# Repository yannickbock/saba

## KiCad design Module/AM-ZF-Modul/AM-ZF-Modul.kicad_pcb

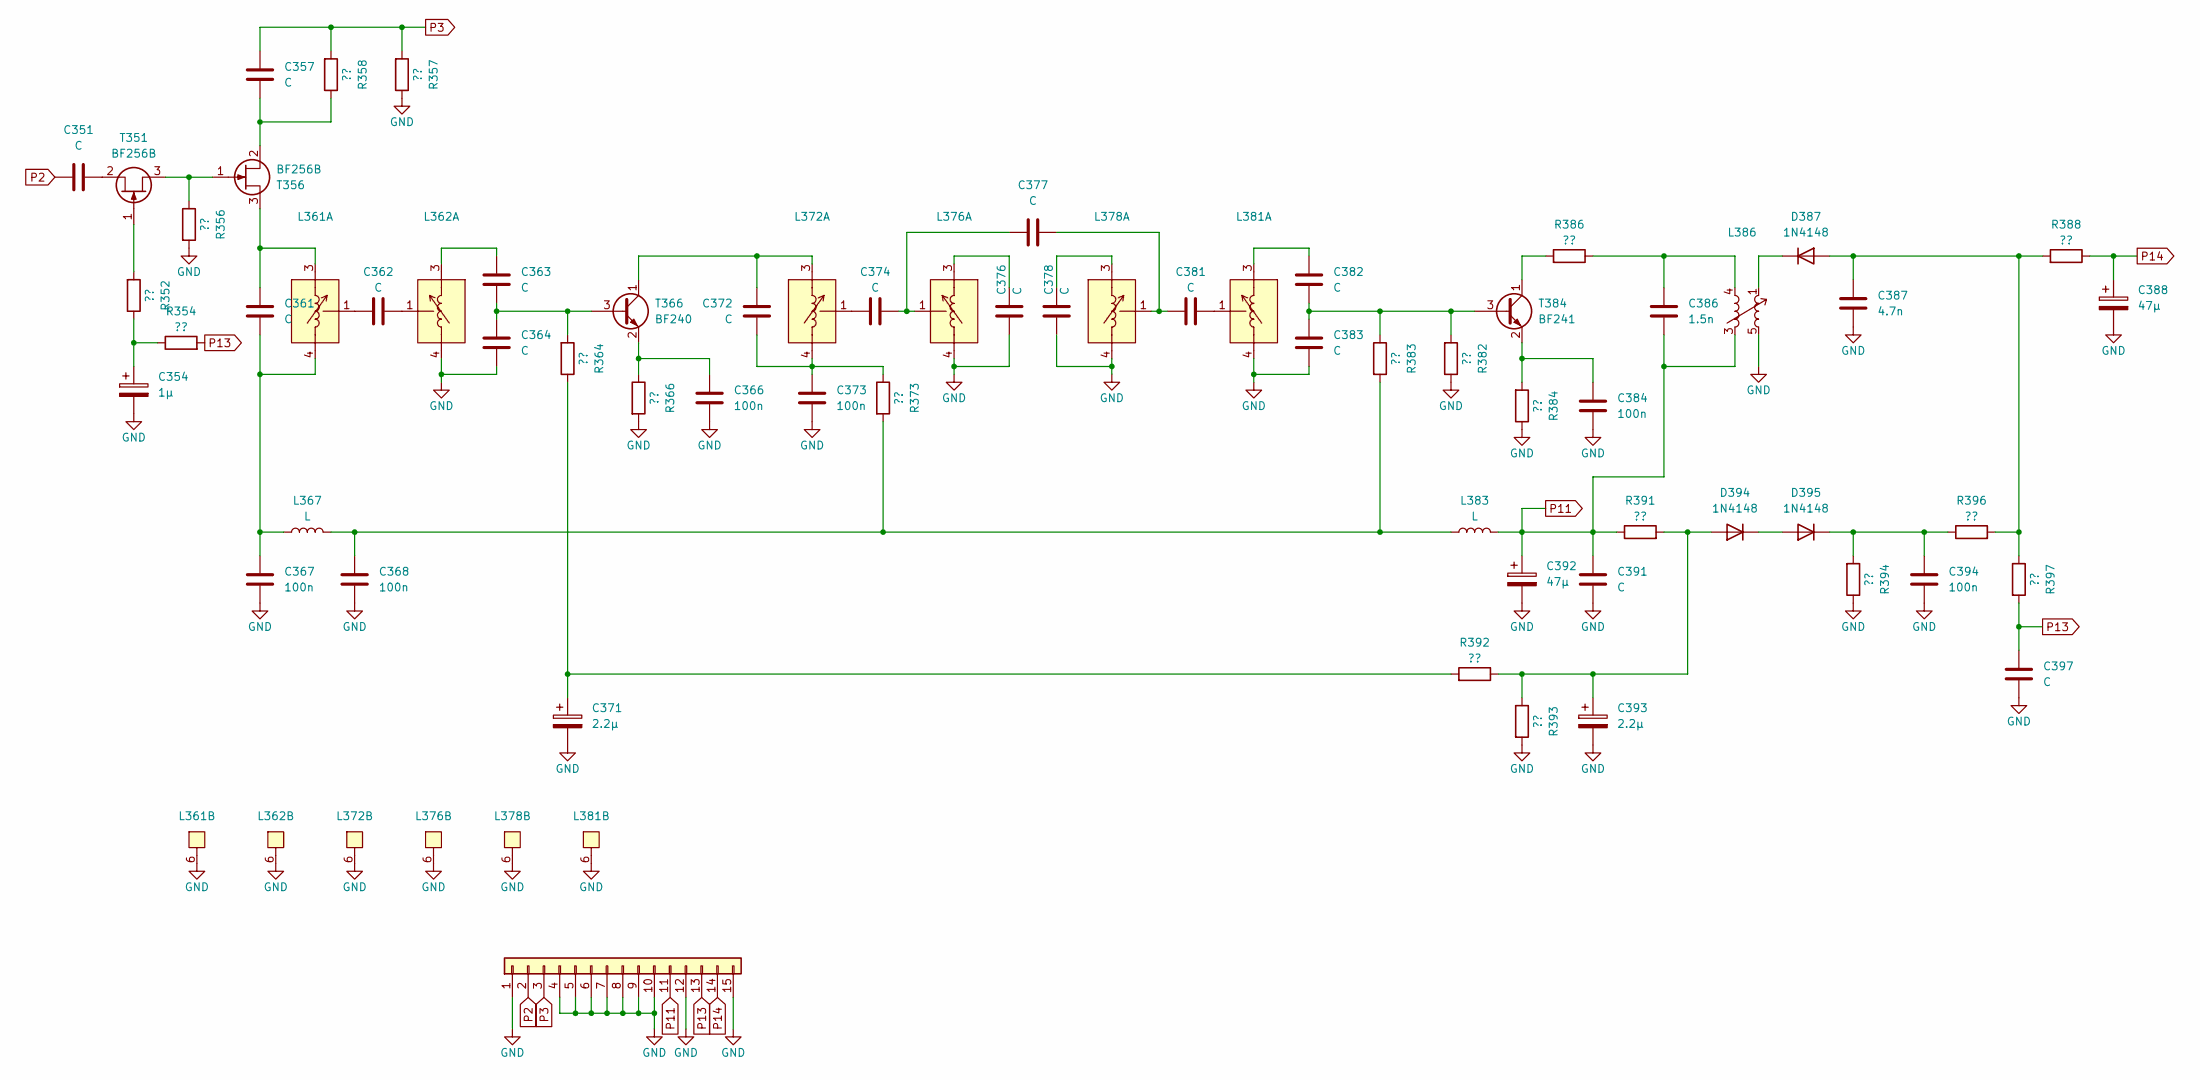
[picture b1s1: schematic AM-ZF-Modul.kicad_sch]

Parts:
C351, C397: C; C_Disc_D4.3mm_W1.9mm_P5.00mm
C354: 1µ; C_Rect_L7.2mm_W7.2mm_P5.00mm_FKS2_FKP2_MKS2_MKP2
C357, C364, C383: C; C_Rect_L7.0mm_W2.5mm_P5.00mm
C361, C362, C363, C372, C374, C376, C377, C378, C381, C382: C; L_Axial_L7.0mm_D3.3mm_P5.08mm_Vertical_Fastron_MICC
C366, C367, C368, C373, C384: 100n; C_Rect_L7.0mm_W2.5mm_P5.00mm
C371, C393: 2.2µ; CP_Radial_D5.0mm_P2.00mm
C386: 1.5n; L_Axial_L7.0mm_D3.3mm_P5.08mm_Vertical_Fastron_MICC
C387: 4.7n; C_Disc_D4.3mm_W1.9mm_P5.00mm
C388, C392: 47µ; CP_Radial_D6.3mm_P2.50mm
C391: C; C_Rect_L7.2mm_W4.5mm_P5.00mm_FKS2_FKP2_MKS2_MKP2
C394: 100n; C_Disc_D4.3mm_W1.9mm_P5.00mm
D387, D394, D395: 1N4148; D_DO-35_SOD27_P5.08mm_Vertical_AnodeUp
J1: Conn_01x15; Connector_01x15_5mm
L361, L362, L378, L381: (no value)
L367, L383: L; L_Axial_L7.0mm_D3.3mm_P5.08mm_Vertical_Fastron_MICC
L372, L376: Inductor_Adjustable_7.5mm
L386: L_Adjustable_4Pin; Inductor_Adjustable_7.5mm
R352, R354, R356, R357, R358, R364, R366, R373, R382, R383, R384, R386, R388, R391, R392, R393, R394, R396, R397: ??; R_Axial_DIN0207_L6.3mm_D2.5mm_P5.08mm_Vertical
T351, T356: BF256B; TO-92_Wide
T366: BF240; TO-92_Wide
T384: BF241; TO-92_Wide

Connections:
GND: C354.2, C364.2, C366.2, C367.2, C368.2, C371.2, C373.2, C376.2, C378.2, C383.2, C384.2, C387.2, C388.2, C391.2, C392.2, C393.2, C394.2, C397.2, J1.1, J1.4, J1.5, J1.6, J1.7, J1.8, J1.9, J1.10, J1.12, J1.15, L361.6, L362.4, L362.6, L372.6, L376.4, L376.6, L378.4, L378.6, L381.4, L381.6, L386.5, L386.6, R356.2, R357.1, R366.2, R382.1, R384.1, R393.2, R394.1
unnamed: C354.1, R352.1, R354.1
unnamed: C361.2, C367.1, L361.4, L367.2
unnamed: C362.1, L361.1
unnamed: C362.2, L362.1
unnamed: C363.1, L362.3
unnamed: C368.1, L367.1, L383.2, R373.2, R383.2
unnamed: C371.1, R364.1, R392.2
unnamed: C372.2, C373.1, L372.4, R373.1
unnamed: C374.1, L372.1
unnamed: C374.2, C377.1, L376.1
unnamed: C376.1, L376.3
unnamed: C377.2, C381.1, L378.1
unnamed: C378.1, L378.3
unnamed: C381.2, L381.1
unnamed: C382.1, L381.3
unnamed: C386.1, L386.4, R386.1
unnamed: C387.1, D387.2 (A), R388.2, R396.2, R397.1
unnamed: D387.1 (K), L386.1
unnamed: C393.1, D394.2 (A), R391.2, R392.1, R393.1
unnamed: D394.1 (K), D395.2 (A)
unnamed: C394.1, D395.1 (K), R394.2, R396.1
unnamed: R356.1, T351.3 (D), T356.1 (G)
unnamed: R352.2, T351.1 (G)
unnamed: C351.2, T351.2 (S)
unnamed: C361.1, L361.3, T356.3 (D)
unnamed: C357.2, R358.1, T356.2 (S)
unnamed: C363.2, C364.1, R364.2, T366.3 (B)
unnamed: C372.1, L372.3, T366.1 (C)
unnamed: C366.1, R366.1, T366.2 (E)
unnamed: C382.2, C383.1, R382.2, R383.1, T384.3 (B)
unnamed: R386.2, T384.1 (C)
unnamed: C384.1, R384.2, T384.2 (E)
P2: C351.1, J1.2
P3: C357.1, J1.3, R357.2, R358.2
P11: C386.2, C391.1, C392.1, J1.11, L383.1, L386.3, R391.1
P13: C397.1, J1.13, R354.2, R397.2
P14: C388.1, J1.14, R388.1

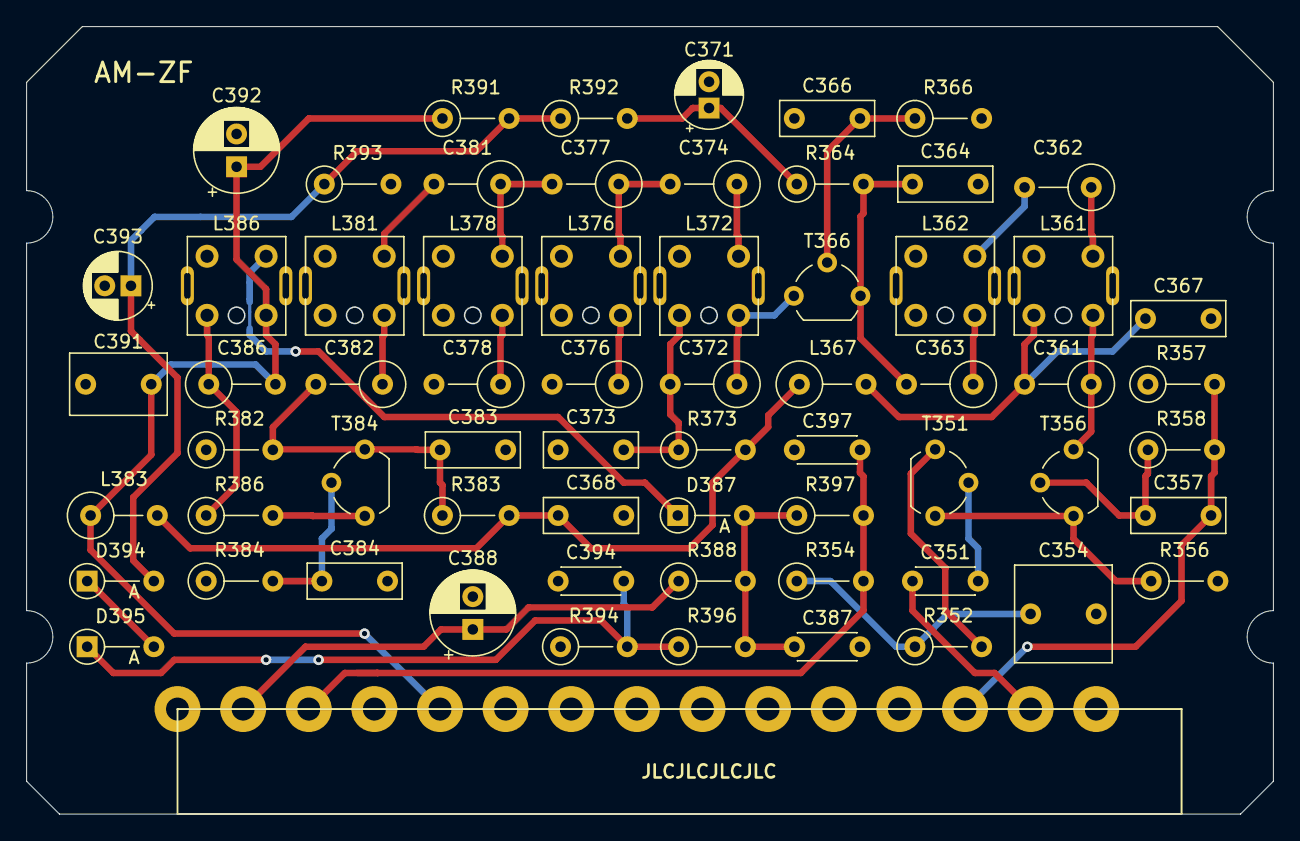
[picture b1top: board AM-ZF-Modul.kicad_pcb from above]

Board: 2 copper layers, 94.9 x 59.9 mm, 65 parts (0 on the bottom side), 38 nets.

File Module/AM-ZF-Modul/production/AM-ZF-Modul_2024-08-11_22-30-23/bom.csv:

Designator,Footprint,Quantity,Value,LCSC Part #
"C351, C397",C_Disc_D4.3mm_W1.9mm_P5.00mm,2,C,
C354,C_Rect_L7.2mm_W7.2mm_P5.00mm_FKS2_FKP2_MKS2_MKP2,1,1µ,
"C357, C364, C383",C_Rect_L7.0mm_W2.5mm_P5.00mm,3,C,
"C361, C362, C363, C372, C374, C376, C377, C378, C381, C382",L_Axial_L7.0mm_D3.3mm_P5.08mm_Vertical_Fastron_MICC,10,C,
"C366, C367, C368, C373, C384",C_Rect_L7.0mm_W2.5mm_P5.00mm,5,100n,
"C371, C393",CP_Radial_D5.0mm_P2.00mm,2,2.2µ,
C386,L_Axial_L7.0mm_D3.3mm_P5.08mm_Vertical_Fastron_MICC,1,1.5n,
C387,C_Disc_D4.3mm_W1.9mm_P5.00mm,1,4.7n,
"C388, C392",CP_Radial_D6.3mm_P2.50mm,2,47µ,
C391,C_Rect_L7.2mm_W4.5mm_P5.00mm_FKS2_FKP2_MKS2_MKP2,1,C,
C394,C_Disc_D4.3mm_W1.9mm_P5.00mm,1,100n,
"D387, D394, D395",D_DO-35_SOD27_P5.08mm_Vertical_AnodeUp,3,1N4148,
J1,Connector_01x15_5mm,1,Conn_01x15,
"L361, L362, L378, L381",Inductor_Adjustable_7.5mm,4,~,
"L367, L383",L_Axial_L7.0mm_D3.3mm_P5.08mm_Vertical_Fastron_MICC,2,L,
"L372, L376",Inductor_Adjustable_7.5mm,2,~,
L386,Inductor_Adjustable_7.5mm,1,L_Adjustable_4Pin,
"R352, R354, R356, R357, R358, R364, R382, R383, R386, R388, R391, R392, R393, R394, R397",R_Axial_DIN0207_L6.3mm_D2.5mm_P5.08mm_Vertical,15,??,
"R366, R373, R384, R396",R_Axial_DIN0207_L6.3mm_D2.5mm_P5.08mm_Vertical,4,??,
"T351, T356",TO-92_Wide,2,BF256B,
T366,TO-92_Wide,1,BF240,
T384,TO-92_Wide,1,BF241,

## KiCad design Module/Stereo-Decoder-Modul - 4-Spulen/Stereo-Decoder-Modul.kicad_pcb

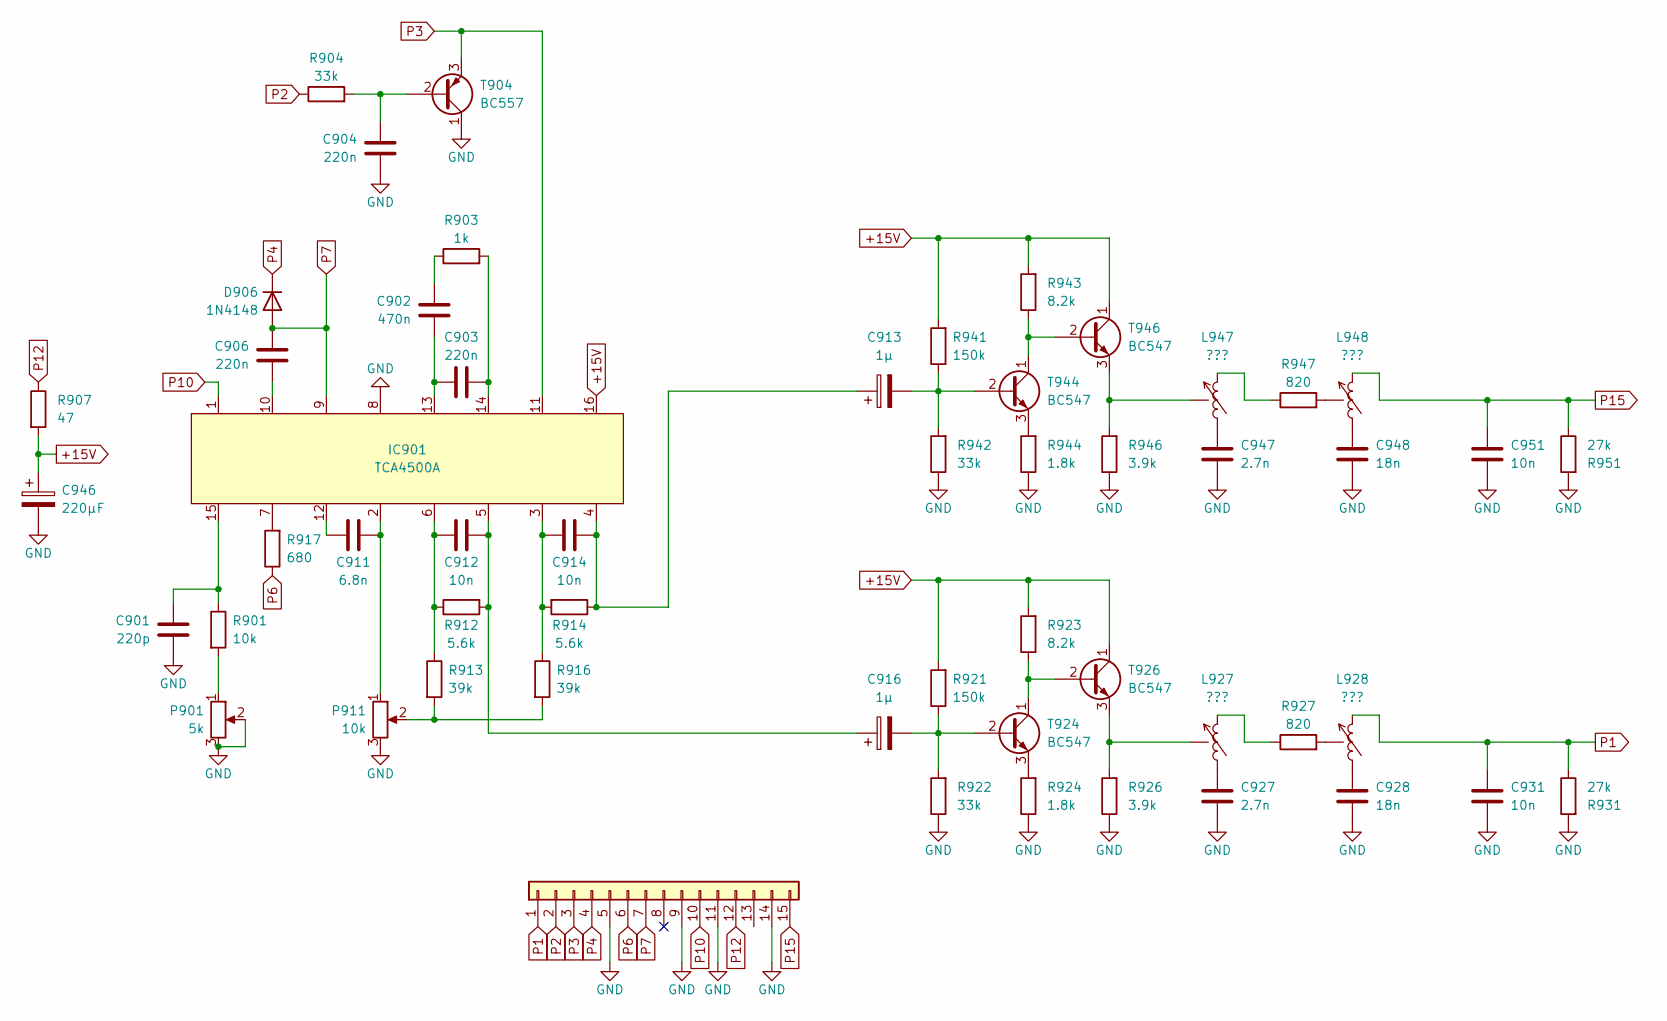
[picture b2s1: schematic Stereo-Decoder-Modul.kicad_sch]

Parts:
C901: 220p; C_Rect_L7.2mm_W3.0mm_P5.00mm_FKS2_FKP2_MKS2_MKP2
C902: 470n; C_Rect_L7.2mm_W3.0mm_P5.00mm_FKS2_FKP2_MKS2_MKP2
C903, C904, C906: 220n; C_Rect_L7.2mm_W3.0mm_P5.00mm_FKS2_FKP2_MKS2_MKP2
C911: 6.8n; C_Rect_L7.2mm_W3.5mm_P5.00mm_FKS2_FKP2_MKS2_MKP2
C912, C914: 10n; C_Rect_L7.2mm_W2.5mm_P5.00mm_FKS2_FKP2_MKS2_MKP2
C913, C916: 1µ; C_Rect_L7.2mm_W7.2mm_P5.00mm_FKS2_FKP2_MKS2_MKP2
C927, C947: 2.7n; C_Rect_L10.0mm_W3.0mm_P7.50mm_MKS4
C928, C948: 18n; C_Rect_L10.0mm_W3.0mm_P7.50mm_MKS4
C931, C951: 10n; C_Rect_L10.0mm_W3.0mm_P7.50mm_MKS4
C946: 220µF; CP_Radial_D6.3mm_P2.50mm
D906: 1N4148; D_DO-35_SOD27_P5.08mm_Vertical_AnodeUp
IC901: TCA4500A; DIP-16_W7.62mm_LongPads
J1: Conn_01x15; Connector_01x15_5mm
L927, L928, L947, L948: ???; Inductor_Adjustable
P901: 5k; Potentiometer_Piher_PT-10-H01_Horizontal
P911: 10k; Potentiometer_Piher_PT-10-H01_Horizontal
R901: 10k; R_Axial_DIN0207_L6.3mm_D2.5mm_P5.08mm_Vertical
R903: 1k; R_Axial_DIN0207_L6.3mm_D2.5mm_P5.08mm_Vertical
R904, R922, R942: 33k; R_Axial_DIN0207_L6.3mm_D2.5mm_P5.08mm_Vertical
R907: 47; R_Axial_DIN0207_L6.3mm_D2.5mm_P5.08mm_Vertical
R912, R914: 5.6k; R_Axial_DIN0207_L6.3mm_D2.5mm_P2.54mm_Vertical
R913, R916: 39k; R_Axial_DIN0207_L6.3mm_D2.5mm_P5.08mm_Vertical
R917: 680; R_Axial_DIN0207_L6.3mm_D2.5mm_P5.08mm_Vertical
R921, R941: 150k; R_Axial_DIN0207_L6.3mm_D2.5mm_P5.08mm_Vertical
R923, R943: 8.2k; R_Axial_DIN0207_L6.3mm_D2.5mm_P5.08mm_Vertical
R924, R944: 1.8k; R_Axial_DIN0207_L6.3mm_D2.5mm_P5.08mm_Vertical
R926, R946: 3.9k; R_Axial_DIN0207_L6.3mm_D2.5mm_P5.08mm_Vertical
R927, R947: 820; R_Axial_DIN0207_L6.3mm_D2.5mm_P5.08mm_Vertical
R931, R951: 27k; R_Axial_DIN0207_L6.3mm_D2.5mm_P5.08mm_Vertical
T904: BC557; TO-92_Wide
T924, T926, T944, T946: BC547; TO-92_Wide

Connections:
+15V: C946.1, IC901.16, R907.2, R921.2, R923.2, R941.2, R943.2, T926.1 (C), T946.1 (C)
GND: C901.1, C904.2, C927.2, C928.2, C931.2, C946.2, C947.2, C948.2, C951.2, IC901.8, J1.5, J1.9, J1.11, J1.14, P901.2, P901.3, P911.3, R922.1, R924.1, R926.1, R931.2, R942.1, R944.1, R946.1, R951.2, T904.1 (C)
unnamed: C901.2, IC901.15, R901.1
unnamed: C902.1, R903.1
unnamed: C902.2, C903.1, IC901.13
unnamed: C903.2, IC901.14, R903.2
unnamed: C906.2, IC901.10
unnamed: C911.1, IC901.12
unnamed: C911.2, IC901.2, P911.1
unnamed: C912.1, C916.1, IC901.5, R912.2
unnamed: C912.2, IC901.6, R912.1, R913.1
unnamed: C913.1, C914.2, IC901.4, R914.1
unnamed: C914.1, IC901.3, R914.2, R916.1
unnamed: C927.1, L927.1
unnamed: C928.1, L928.1
unnamed: C947.1, L947.1
unnamed: C948.1, L948.1
unnamed: IC901.7, R917.2
unnamed: L927.3, R927.1
unnamed: L928.2, R927.2
unnamed: L947.3, R947.1
unnamed: L948.2, R947.2
unnamed: P901.1, R901.2
unnamed: P911.2, R913.2, R916.2
unnamed: C904.1, R904.2, T904.2 (B)
unnamed: C916.2, R921.1, R922.2, T924.2 (B)
unnamed: R923.1, T924.1 (C), T926.2 (B)
unnamed: R924.2, T924.3 (E)
unnamed: L927.2, R926.2, T926.3 (E)
unnamed: C913.2, R941.1, R942.2, T944.2 (B)
unnamed: R943.1, T944.1 (C), T946.2 (B)
unnamed: R944.2, T944.3 (E)
unnamed: L947.2, R946.2, T946.3 (E)
P1: C931.1, J1.1, L928.3, R931.1
P2: J1.2, R904.1
P3: IC901.11, J1.3, T904.3 (E)
P4: D906.1 (K), J1.4
P6: J1.6, R917.1
P7: C906.1, D906.2 (A), IC901.9, J1.7
P10: IC901.1, J1.10
P12: J1.12, R907.1
P15: C951.1, J1.15, L948.3, R951.1

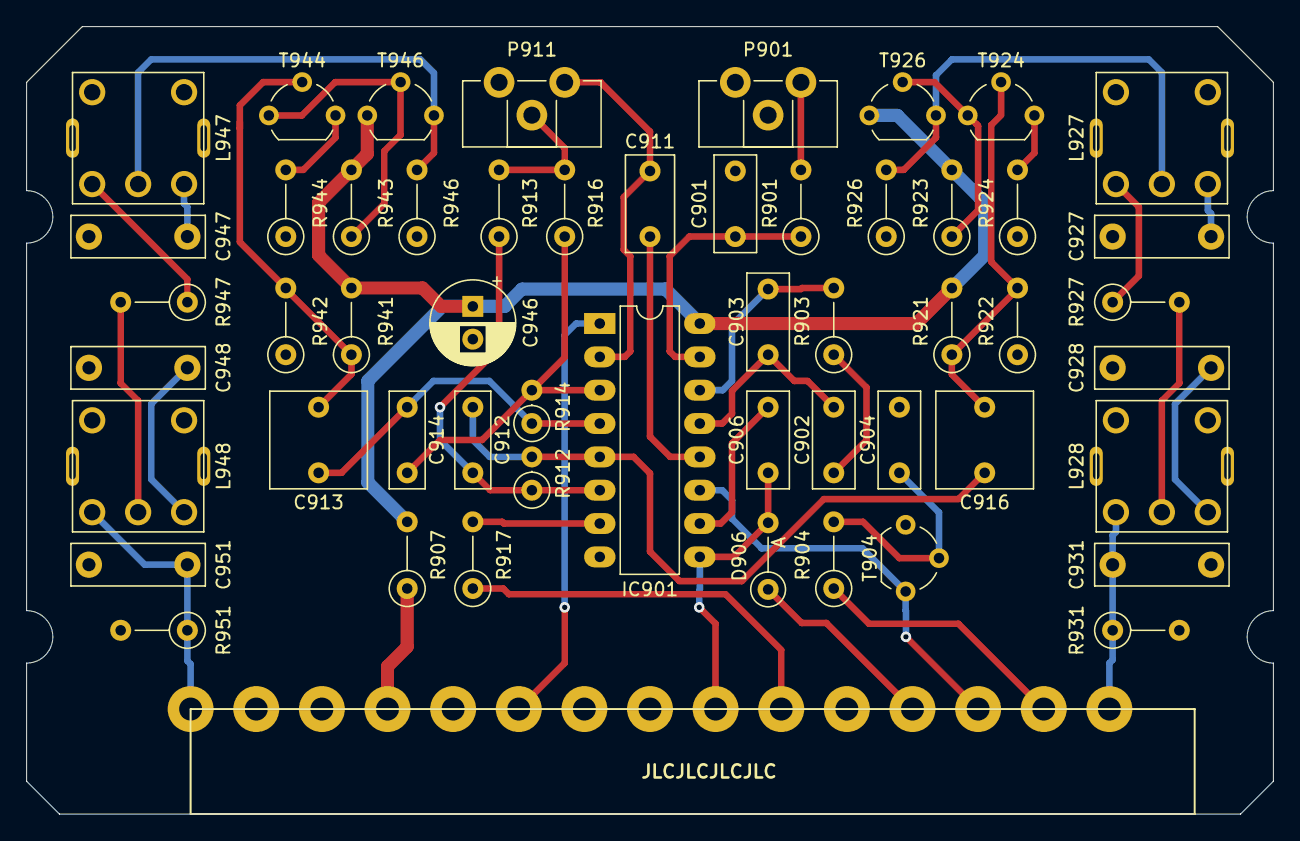
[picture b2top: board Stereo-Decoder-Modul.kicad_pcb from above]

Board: 2 copper layers, 95.0 x 60.0 mm, 54 parts (0 on the bottom side), 42 nets.

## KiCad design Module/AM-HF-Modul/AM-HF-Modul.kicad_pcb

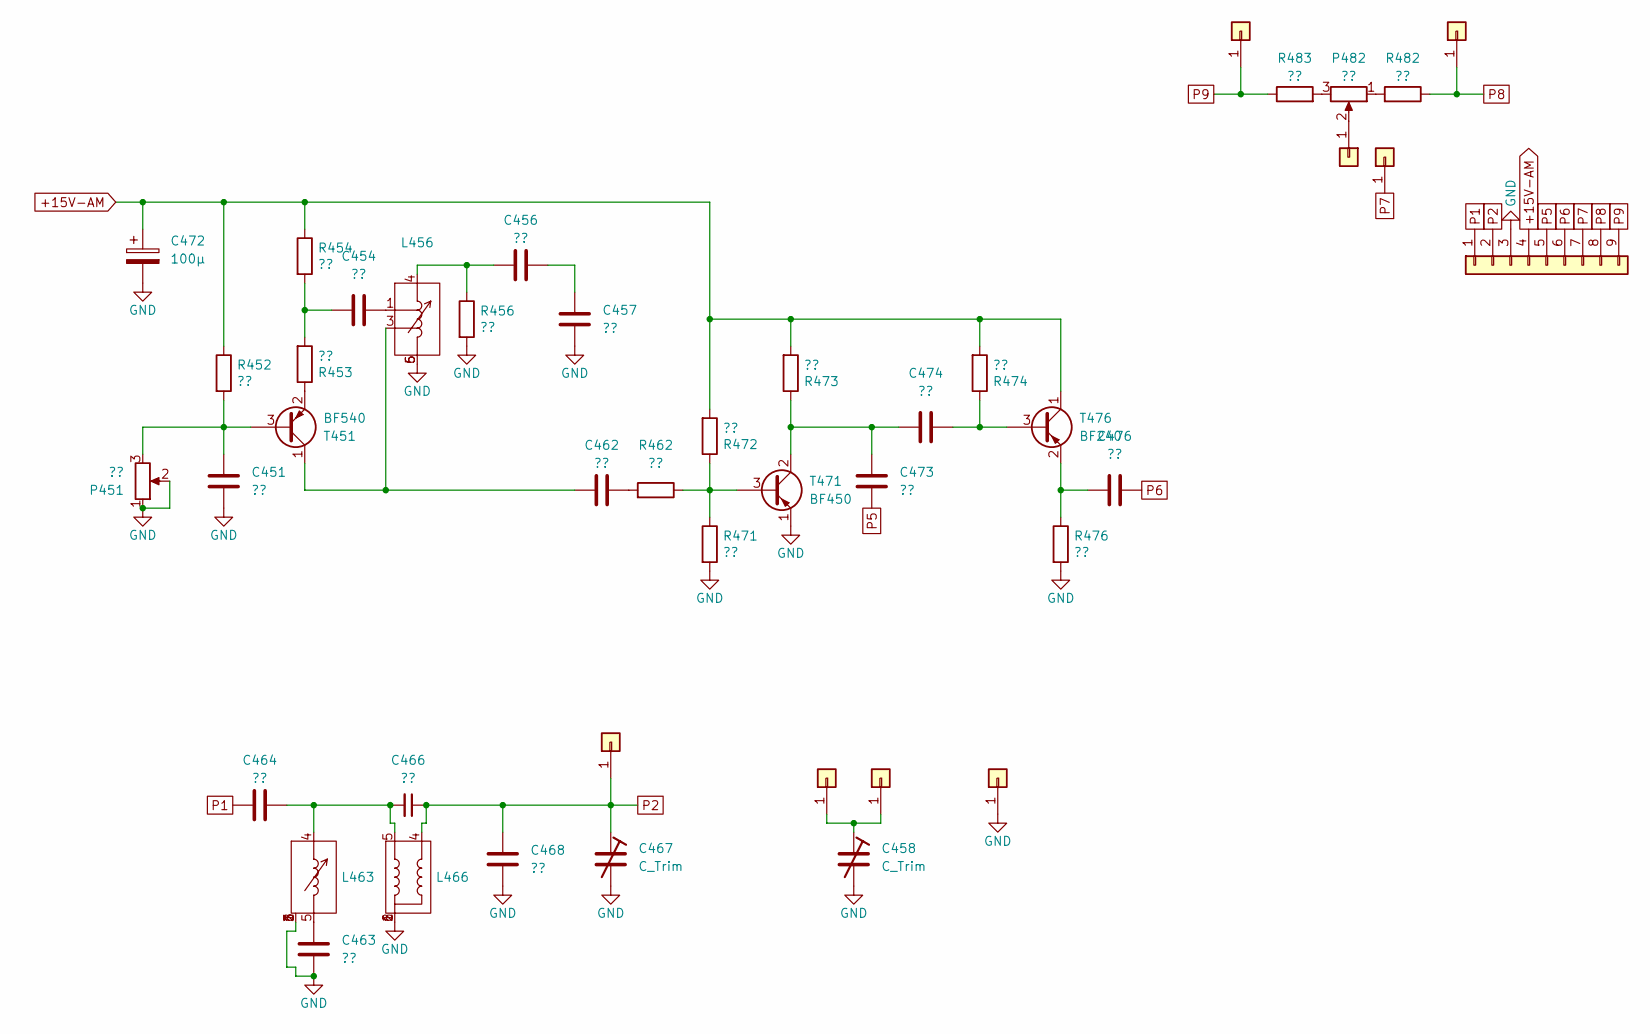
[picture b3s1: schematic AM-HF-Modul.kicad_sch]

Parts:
C451, C454, C456, C457, C462, C463, C464, C466, C468, C474, C476: ??; C_Disc_D4.3mm_W1.9mm_P5.00mm
C458, C467: C_Trim; C_Trimmable_7.5mm
C472: 100µ; CP_Radial_D6.3mm_P2.50mm
C473: ??; C_Rect_L7.2mm_W2.5mm_P5.00mm_FKS2_FKP2_MKS2_MKP2
J1: Conn_01x09; Connector_01x09_5mm
J2, J3, J4, J5, J6, J7, J8: Conn_01x01; Pin_D1.0mm_L10.0mm
J9: Conn_01x01; Connector_01x01_Rect
L456: L_Trimmable_Type3; L_Tunable_7mm
L463: L_Trimmable_Type1; L_Tunable_7mm
L466: L_Trimmable_Type2; L_Tunable_16.5mm
P451, P482: ??; Potentiometer_Piher_PT-10-H01_Horizontal
R452, R453, R454, R456, R462, R471, R472, R473, R474, R476, R482, R483: ??; R_Axial_DIN0207_L6.3mm_D2.5mm_P5.08mm_Vertical
T451: BF540; TO-92L_Wide
T471: BF450; TO-92L_Wide
T476: BF240; TO-92L_Wide

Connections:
+15V-AM: C472.1, J1.4, R452.1, R454.1, R472.2, R473.2, R474.2, T476.1 (C)
GND: C451.1, C457.1, C458.2, C463.1, C467.2, C468.1, C472.2, J1.3, J9.1, L456.5, L456.6, L463.1, L463.2, L463.3, L463.6, L466.1, L466.2, L466.6, P451.1, P451.2, R456.2, R471.2, R476.2, T471.1 (E)
unnamed: C454.1, L456.1
unnamed: C454.2, R453.2, R454.2
unnamed: C456.1, C457.2
unnamed: C456.2, L456.4, R456.1
unnamed: C462.1, R462.2
unnamed: C463.2, L463.5
unnamed: C464.1, C466.2, L463.4, L466.5
unnamed: J4.1, P482.2
unnamed: C458.1, J6.1, J7.1
unnamed: P482.1, R482.2
unnamed: P482.3, R483.2
unnamed: C451.2, P451.3, R452.2, T451.3 (B)
unnamed: C462.2, L456.3, T451.1 (C)
unnamed: R453.1, T451.2 (E)
unnamed: R462.1, R471.1, R472.1, T471.3 (B)
unnamed: C473.2, C474.2, R473.1, T471.2 (C)
unnamed: C474.1, R474.1, T476.3 (B)
unnamed: C476.2, R476.1, T476.2 (E)
P1: C464.2, J1.1
P2: C466.1, C467.1, C468.2, J1.2, J8.1, L466.4
P5: C473.1, J1.5
P6: C476.1, J1.6
P7: J1.7, J5.1
P8: J1.8, J2.1, R482.1
P9: J1.9, J3.1, R483.1

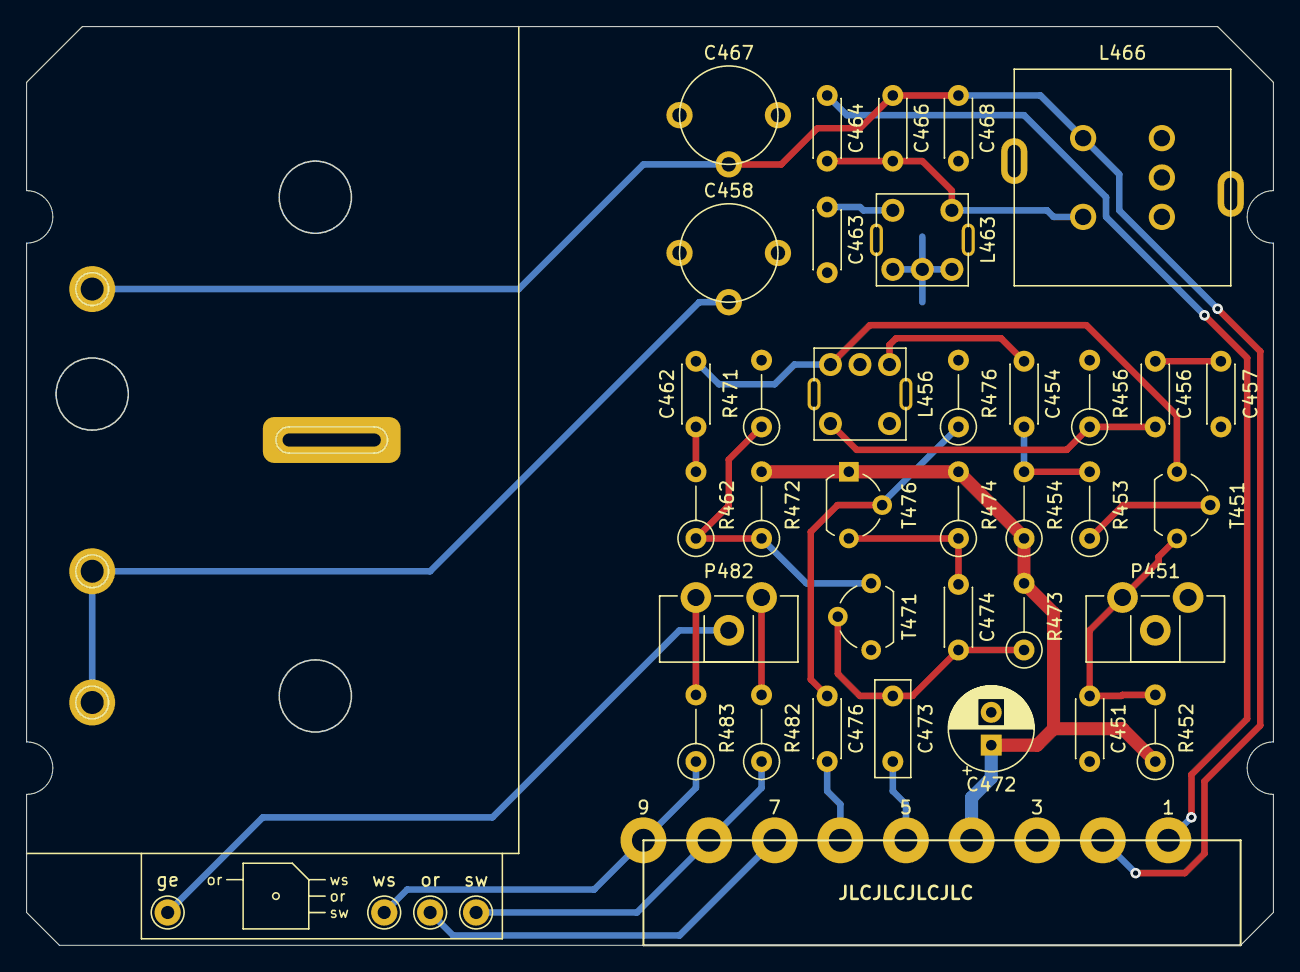
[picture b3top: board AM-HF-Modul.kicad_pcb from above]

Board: 2 copper layers, 94.9 x 69.9 mm, 44 parts (0 on the bottom side), 27 nets.

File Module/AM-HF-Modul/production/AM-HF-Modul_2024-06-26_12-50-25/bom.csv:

Designator,Footprint,Quantity,Value,LCSC Part #
"C451, C454, C456, C457, C462, C463, C464, C466, C468, C474, C476",C_Disc_D4.3mm_W1.9mm_P5.00mm,11,??,
"C458, C467",C_Trimmable_7.5mm,2,C_Trim,
C472,CP_Radial_D6.3mm_P2.50mm,1,100µ,
C473,C_Rect_L7.2mm_W2.5mm_P5.00mm_FKS2_FKP2_MKS2_MKP2,1,??,
J1,Connector_01x09_5mm,1,Conn_01x09,
"J2, J3, J4, J5, J6, J7, J8",Pin_D1.0mm_L10.0mm,7,Conn_01x01,
J9,Connector_01x01_Rect,1,Conn_01x01,
L456,L_Tunable_7mm,1,L_Trimmable_Type3,
L463,L_Tunable_7mm,1,L_Trimmable_Type1,
L466,L_Tunable_16.5mm,1,L_Trimmable_Type2,
"P451, P482",Potentiometer_Piher_PT-10-H01_Horizontal,2,??,
"R452, R453, R454, R456, R462, R471, R472, R473, R474, R476",R_Axial_DIN0207_L6.3mm_D2.5mm_P5.08mm_Vertical,10,??,
"R482, R483",R_Axial_DIN0207_L6.3mm_D2.5mm_P5.08mm_Vertical,2,??,
T451,TO-92L_Wide,1,BF540,
T471,TO-92L_Wide,1,BF450,
T476,TO-92L_Wide,1,BF240,
